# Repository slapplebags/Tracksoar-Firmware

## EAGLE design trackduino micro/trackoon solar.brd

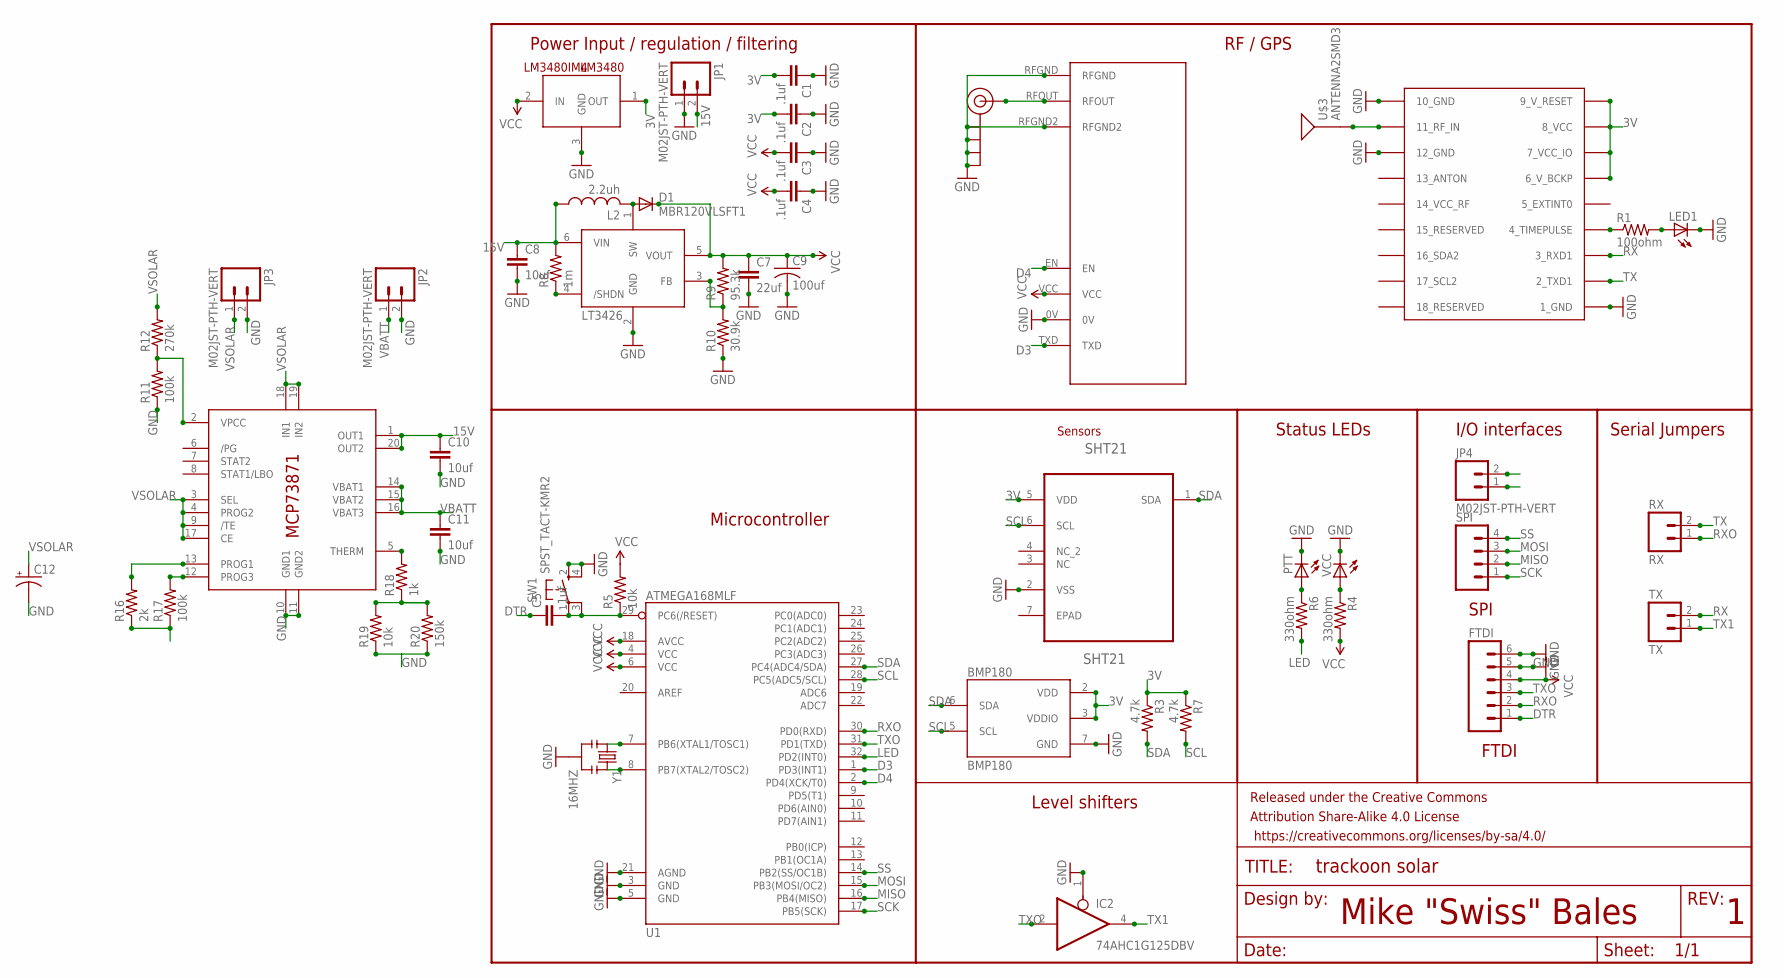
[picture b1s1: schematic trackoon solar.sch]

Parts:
BMP180: BMP180
C1, C2, C3, C4, C5: .1uf; 0805
C7: 22uf; 0805
C8, C10, C11: 10uf; 0805
C9: 100uf; C1206
C12: CPOL-US153CLV-1012; 153CLV-1012
D1: MBR120VLSFT1; SOD123
FRAME1: FRAME-LETTER; CREATIVE_COMMONS
FTDI: M06NO_SILK_FEMALE_PTH; 1X06_NO_SILK
IC1: MCP73871; QFN20
IC2: 74AHC1G125DBV; SOT23-5
J$1: SMA_EDGE; SMA-EDGE
JP1, JP2, JP3, JP4: M02JST-PTH-VERT; JST-2-PTH-VERT
L2: 2.2uh; L1812
LED1: LEDCHIP-LED0805; CHIP-LED0805
LM3480: LM3480IM4; SOT23-3
LT3426: LT3426; SOT23-6
PTT: LEDCHIP-LED0805; CHIP-LED0805
R1: 100ohm; 0805
R3, R7: 4.7k; 0805
R4, R6: 330ohm; 0805
R5, R19: 10k; 0805
R8: 1m; 0805
R9: 95.3k; 0805
R10: 30.9k; 0805
R11, R17: 100k; 0805
R12: 270k; 0805
R16: 2k; 0805
R18: 1k; 0805
R20: 150k; 0805
RX: RX; 1X02
SHT21: SHT21; DFN300X300X110-7N
SPI: M04JST-PTH-VERT; JST-4-PTH-VERT
SW1: SPST_TACT-KMR2; KMR2
TX: TX; 1X02
U1: ATMEGA168MLF; MLF32
U$1: UBLOX_MAX
U$2: RADIOMETRIX-HX1
U$3: ANTENNA2SMD3; ANTENNA-CHIP4
VCC: LEDCHIP-LED0805; CHIP-LED0805
Y1: 16MHZ; RESONATOR-SMD

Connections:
3V: BMP180.2 (VDD), BMP180.3 (VDDIO), C1.2, C2.2, LM3480.1 (OUT), R3.1, R7.1, SHT21.5 (VDD), U$1.6_V_BCKP, U$1.7_VCC_IO, U$1.8_VCC, U$1.9_V_RESET
15V: C8.1, C10.1, IC1.1 (OUT1), IC1.20 (OUT2), JP1.2, L2.1, LT3426.6 (VIN), R8.2
D3: U1.1 (PD3(INT1)), U$2.TXD
D4: U1.2 (PD4(XCK/T0)), U$2.EN
DTR: C5.1, FTDI.1
GND: BMP180.7 (GND), C1.1, C2.1, C3.1, C4.1, C7.2, C8.2, C9.2, C10.2, C11.2, C12.-, FTDI.5, FTDI.6, IC1.10 (GND1), IC1.11 (GND2), IC2.1 (OE), IC2.3 (GND), J$1.GND@0 (GND), J$1.GND@1 (GND), J$1.GND@2 (GND), J$1.GND@3 (GND), JP1.1, JP2.2, JP3.2, LED1.C, LM3480.3 (GND), LT3426.2 (GND), PTT.C, R10.1, R11.1, R16.1, R17.1, R19.1, R20.1, SHT21.2 (VSS), SW1.2 (S), SW1.4 (S1), U1.3 (GND), U1.5 (GND), U1.21 (AGND), U$1.1_GND, U$1.10_GND, U$1.12_GND, U$2.0V, U$2.RFGND, U$2.RFGND2, VCC.C, Y1.2
LED: R6.2, U1.32 (PD2(INT0))
MISO: SPI.2, U1.16 (PB4(MISO))
MOSI: SPI.3, U1.15 (PB3(MOSI/OC2))
unnamed: J$1.SIG (SIGNAL), U$2.RFOUT
unnamed: R1.1, U$1.4_TIMEPULSE
unnamed: LED1.A, R1.2
unnamed: U$1.11_RF_IN, U$3.SIG
unnamed: R4.1, VCC.A
unnamed: D1.A, L2.2, LT3426.1 (SW)
unnamed: LT3426.4 (/SHDN), R8.1
unnamed: LT3426.3 (FB), R9.1, R10.2
unnamed: U1.8 (PB7(XTAL2/TOSC2)), Y1.3
unnamed: IC1.2 (VPCC), R11.2, R12.1
unnamed: C5.2, R5.1, SW1.1, SW1.3 (P1), U1.29 (PC6(/RESET))
unnamed: IC1.13 (PROG1), R16.2
unnamed: IC1.12 (PROG3), R17.2
unnamed: U1.7 (PB6(XTAL1/TOSC1)), Y1.1
unnamed: PTT.A, R6.1
unnamed: IC1.5 (THERM), R18.2
unnamed: R18.1, R19.2, R20.2
RX: TX.2, U$1.3_RXD1
RXO: FTDI.2, RX.1, U1.30 (PD0(RXD))
SCK: SPI.1, U1.17 (PB5(SCK))
SCL: BMP180.5 (SCL), JP4.1, R7.2, SHT21.6 (SCL), U1.28 (PC5(ADC5/SCL))
SDA: BMP180.6 (SDA), JP4.2, R3.2, SHT21.1 (SDA), U1.27 (PC4(ADC4/SDA))
SS: SPI.4, U1.14 (PB2(SS/OC1B))
TX: RX.2, U$1.2_TXD1
TX1: IC2.4 (O), TX.1
TXO: FTDI.3, IC2.2 (I), U1.31 (PD1(TXD))
VBATT: C11.1, IC1.14 (VBAT1), IC1.15 (VBAT2), IC1.16 (VBAT3), JP2.1
VCC: C3.2, C4.2, C7.1, C9.1, D1.C, FTDI.4, IC2.5 (VCC), LM3480.2 (IN), LT3426.5 (VOUT), R4.2, R5.2, R9.2, U1.4 (VCC), U1.6 (VCC), U1.18 (AVCC), U$2.VCC
VSOLAR: C12.+, IC1.3 (SEL), IC1.4 (PROG2), IC1.9 (/TE), IC1.17 (CE), IC1.18 (IN1), IC1.19 (IN2), JP3.1, R12.2

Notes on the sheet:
Mike "Swiss" Bales
Power Input / regulation / filtering
RF / GPS
Microcontroller
Level shifters
Status LEDs
I/O interfaces
Serial Jumpers
SPI
FTDI
Sensors

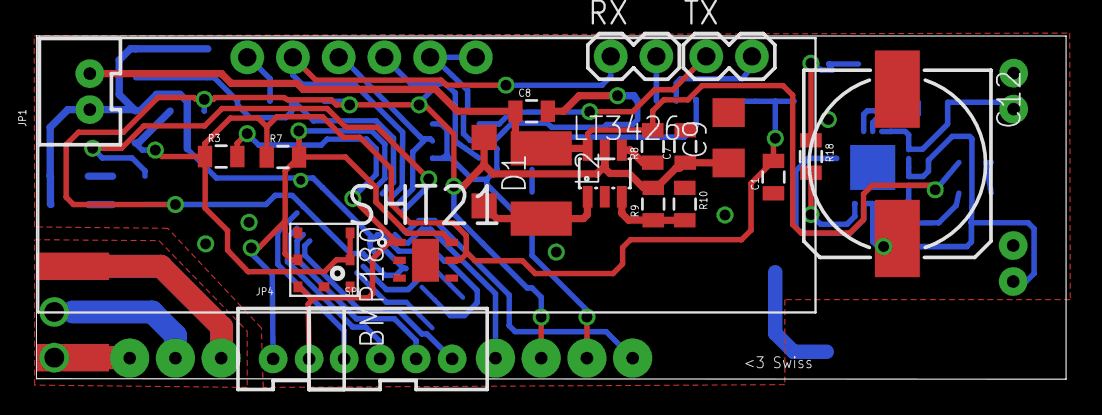
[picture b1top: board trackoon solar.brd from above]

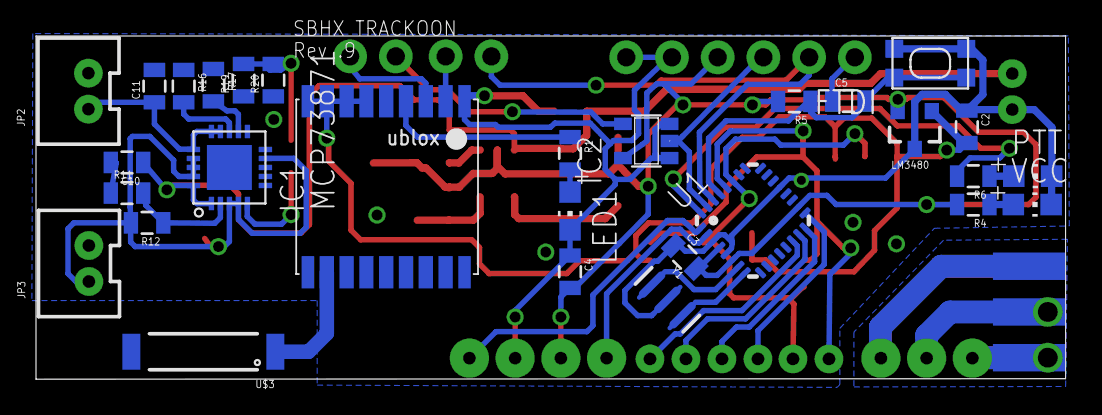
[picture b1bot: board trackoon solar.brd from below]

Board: 2 copper layers, 57.2 x 19.1 mm, 54 parts (31 on the bottom side), 38 nets.

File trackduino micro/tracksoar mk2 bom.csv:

"Part";"Value";"Device";"Package";"Description";"MPN";"OC_FARNELL";"OC_NEWARK";"PACKAGE";"PROD_ID";"SUPPLIER";"VALUE";
"BMP180";"BMP180";"BMP180";"BMP180";"BOSCH BMP180 DIGITAL BAROMETRIC PRESSURE SENSOR";"";"";"";"";"";"";"";
"C1";".1uf";"CAP0805";"0805";"Capacitor";"";"";"";"";"";"";"";
"C2";".1uf";"CAP0805";"0805";"Capacitor";"";"";"";"";"";"";"";
"C3";".1uf";"CAP0805";"0805";"Capacitor";"";"";"";"";"";"";"";
"C4";".1uf";"CAP0805";"0805";"Capacitor";"";"";"";"";"";"";"";
"C5";".1uf";"CAP0805";"0805";"Capacitor";"";"";"";"";"";"";"";
"C7";"22uf";"CAP0805";"0805";"Capacitor";"";"";"";"";"";"";"";
"C8";"10uf";"CAP0805";"0805";"Capacitor";"";"";"";"";"";"";"";
"C9";"100uf";"C-USC1206";"C1206";"CAPACITOR, American symbol";"";"";"";"";"";"";"";
"D1";"MBR120VLSFT1";"DIODE-SOD123";"SOD123";"DIODE";"";"";"";"";"";"";"";
"FRAME1";"FRAME-LETTER";"FRAME-LETTER";"CREATIVE_COMMONS";"Schematic Frame";"";"";"";"";"";"";"";
"FTDI";"";"M06NO_SILK_FEMALE_PTH";"1X06_NO_SILK";"Header 6";"";"";"";"";"CONN-08437";"";"";
"IC2";"74AHC1G125DBV";"74AHC1G125DBV";"SOT23-5";"Single Bus Buffer Gate with 3-State Output";"";"";"";"";"";"";"";
"J$1";"SMA_EDGE";"SMA_EDGE";"SMA-EDGE";"SMA Antenna Connector";"";"";"";"";"";"";"";
"JP1";"M02JST-PTH-VERT";"M02JST-PTH-VERT";"JST-2-PTH-VERT";"Standard 2-pin 0.1" header. Use with";"";"";"";"";"";"";"";
"L2";"2.2uh";"L-USL1812";"L1812";"INDUCTOR, American symbol";"";"";"";"";"";"";"";
"LED1";"";"LEDCHIP-LED0805";"CHIP-LED0805";"LED";"";"";"";"";"";"";"";
"LM3480";"LM3480IM4";"LM3480IM4";"SOT23-3";"Small package linear regulator";"";"";"";"";"";"";"";
"LT3426";"LT3426";"LT3426";"SOT23-6";"LT3426";"";"";"";"";"";"";"";
"PTT";"";"LEDCHIP-LED0805";"CHIP-LED0805";"LED";"";"";"";"";"";"";"";
"R1";"100ohm";"RESISTOR0805-RES";"0805";"Resistor";"";"";"";"";"";"";"";
"R3";"4.7k";"RESISTOR0805-RES";"0805";"Resistor";"";"";"";"";"";"";"";
"R5";"10k";"RESISTOR0805-RES";"0805";"Resistor";"";"";"";"";"";"";"";
"R6";"330ohm";"RESISTOR0805-RES";"0805";"Resistor";"";"";"";"";"";"";"";
"R7";"4.7k";"RESISTOR0805-RES";"0805";"Resistor";"";"";"";"";"";"";"";
"R8";"1m";"RESISTOR0805-RES";"0805";"Resistor";"";"";"";"";"";"";"";
"R9";"95.3k";"RESISTOR0805-RES";"0805";"Resistor";"";"";"";"";"";"";"";
"R10";"30.9k";"RESISTOR0805-RES";"0805";"Resistor";"";"";"";"";"";"";"";
"RX";"RX";"M02JST-PTH-VERT";"JST-2-PTH-VERT";"Standard 2-pin 0.1" header. Use with";"";"";"";"";"";"";"";
"SHT21";"SHT21";"SHT21";"DFN300X300X110-7N";"SENSOR, HUMIDITY & TEMP";"SHT21";"1855468";"20T1172";"DFN-6";"";"SENSIRION";"";
"SPI";"";"M04JST-PTH-VERT";"JST-4-PTH-VERT";"Header 4";"";"";"";"";"";"";"";
"SW1";"SPST_TACT-KMR2";"SPST_TACT-KMR2";"KMR2";"SMT 6mm switch, EVQQ2 series";"";"";"";"";"";"";"";
"TX";"TX";"M02JST-PTH-VERT";"JST-2-PTH-VERT";"Standard 2-pin 0.1" header. Use with";"";"";"";"";"";"";"";
"TX1";"TX";"M02JST-PTH-VERT";"JST-2-PTH-VERT";"Standard 2-pin 0.1" header. Use with";"";"";"";"";"";"";"";
"U$1";"UBLOX_MAX";"UBLOX_MAX";"UBLOX_MAX";"UBLOX MAX";"";"";"";"";"";"";"";
"U$2";"RADIOMETRIX-HX1";"RADIOMETRIX-HX1";"RADIOMETRIX-HX1";"";"";"";"";"";"";"";"";
"U$3";"ANTENNA2SMD3";"ANTENNA2SMD3";"ANTENNA-CHIP4";"Chip antenna";"";"";"";"";"";"";"";
"U1";"ATMEGA168MLF";"ATMEGA168MLF";"MLF32";"Atmel 32-pin 8-bit micro, 16k flash.";"";"";"";"";"";"";"";
"Y1";"16MHZ";"RESONATOR16MHZ";"RESONATOR-SMD";"Resonator";"";"";"";"";"XTAL-08900";"";"16MHZ";

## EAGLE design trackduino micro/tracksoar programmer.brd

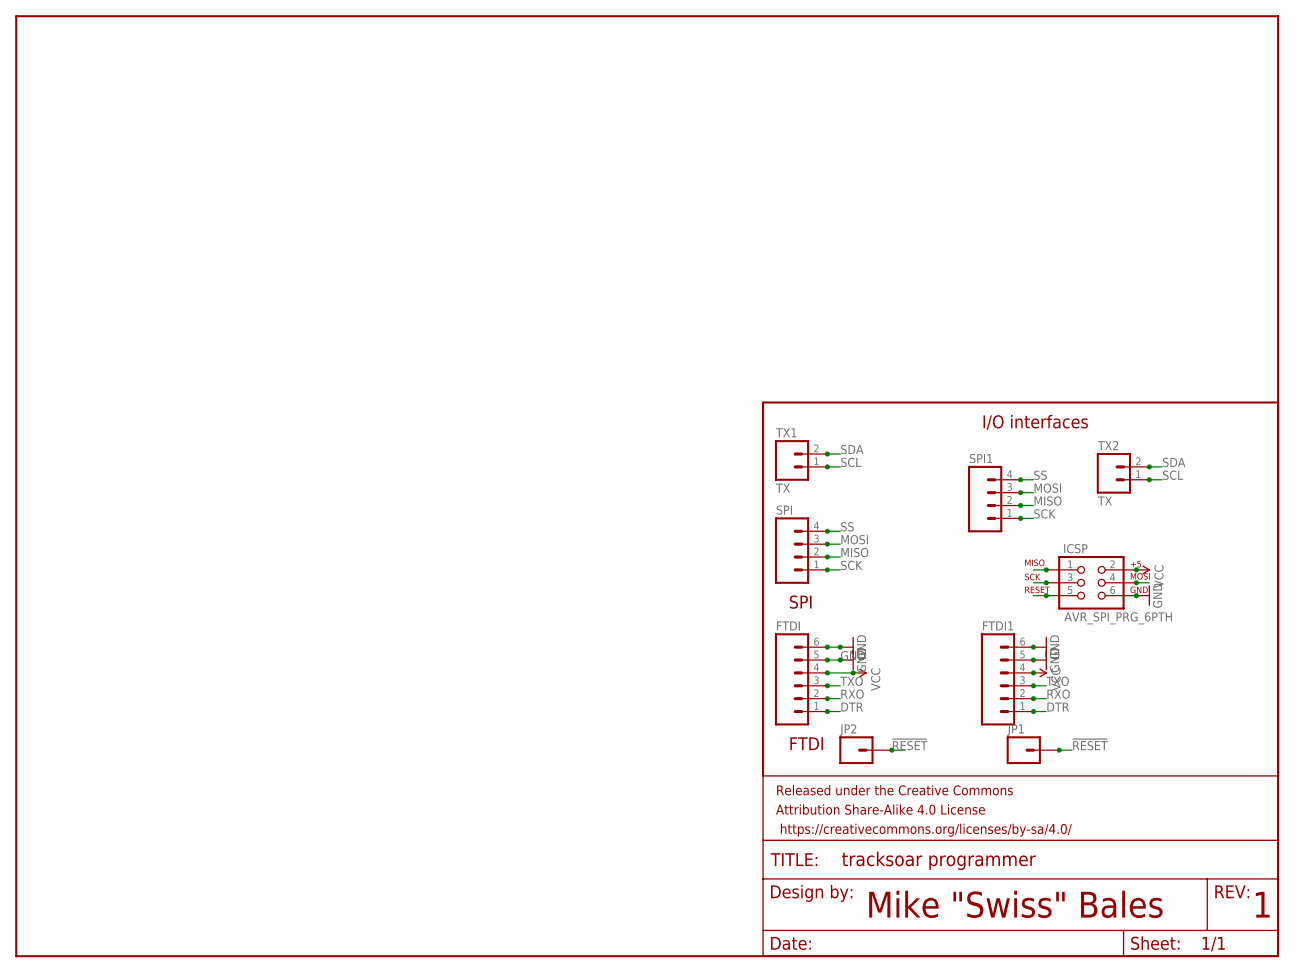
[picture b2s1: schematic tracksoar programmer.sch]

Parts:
FRAME1: FRAME-LETTER; CREATIVE_COMMONS
FTDI, FTDI1: M06NO_SILK_FEMALE_PTH; 1X06_NO_SILK
ICSP: AVR_SPI_PRG_6PTH; 2X3
JP1, JP2: M01PTH; 1X01
SPI, SPI1: M04JST-PTH-VERT; JST-4-PTH-VERT
TX1, TX2: TX; JST-2-PTH-VERT

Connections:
!RESET: ICSP.5, JP1.1, JP2.1
DTR: FTDI.1, FTDI1.1
GND: FTDI.5, FTDI.6, FTDI1.5, FTDI1.6, ICSP.6
MISO: ICSP.1, SPI.2, SPI1.2
MOSI: ICSP.4, SPI.3, SPI1.3
RXO: FTDI.2, FTDI1.2
SCK: ICSP.3, SPI.1, SPI1.1
SCL: TX1.1, TX2.1
SDA: TX1.2, TX2.2
SS: SPI.4, SPI1.4
TXO: FTDI.3, FTDI1.3
VCC: FTDI.4, FTDI1.4, ICSP.2

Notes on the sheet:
Mike "Swiss" Bales
I/O interfaces
SPI
FTDI

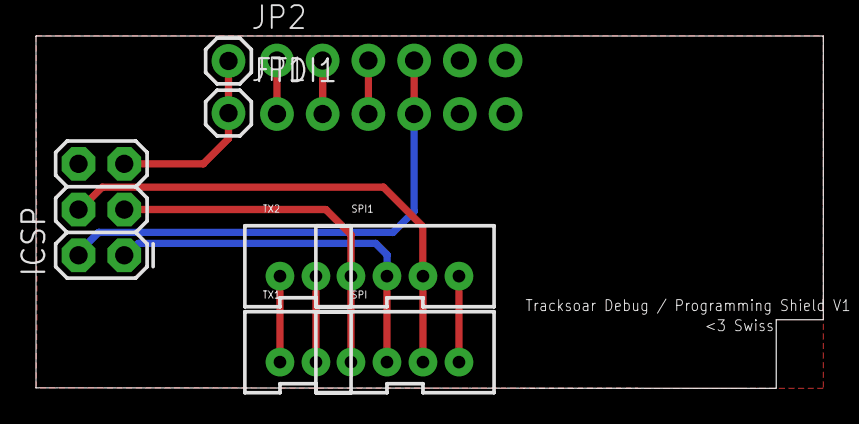
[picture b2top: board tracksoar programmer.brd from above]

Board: 2 copper layers, 43.7 x 19.6 mm, 10 parts (1 on the bottom side), 12 nets.

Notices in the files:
parts and their libraries:
SparkFun-PowerIC: Licensing: Creative Commons ShareAlike 4.0 International - https://creativecommons.org/licenses/by-sa/4.0
SparkFun-Aesthetics: Released under the Creative Commons Attribution Share-Alike 4.0 License
SparkFun-Aesthetics: https://creativecommons.org/licenses/by-sa/4.0
